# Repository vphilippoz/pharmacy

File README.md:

# Pharmacy Cross Display
<p align="left">
    
</p>

A miniature pharmacy cross display made of LED matrices.

This is a fun project to build and decorate you home, or bring at a rave party! The software runs on a ESP32 and controls 5 square LED matrices.

# Features

In its current version, the project has:

- 8 animations
- Button to switch between animations
- Potentiometer to tune brightness and animation speed
- Python script to easily create animation bitmap from a .gif file
- Excel file to easily create animation bitmap from a drawing (in excel file)

Available animations are:

1. Always ON
1. Blink
1. Random (White noise)
1. Cross shrinking
1. Girl dance
1. Fortnite dance
1. Spinning fish
1. Spiral

# Usage

Plug the power connector. The device starts automatically. A short press on the button changes the animation. Turning the knob allows to tune the animation speed. One cycle is between 80 BPM and 250 BPM. When holding the button, the knob controlls the display brightness.

# BOM

This list is not intended to be a shopping list. It enumerates everything needed to make the Pharmacy Cross Display, but use what you have and adapt the design as needed.

## Electronics

- 5V power supply
- Custom-made PCBs (one of each)
- ESP32-C6-DevKit
- 3 HT16K33 modules (Adafruit 1427)
- 5 green LED matrices (Adafruit 1623)
- 1 10kOhm rotary potentiometer
- 1 THT 10kOhm resistor
- 1 push button
- 1 barrel power connector
- Cables
- Headers for ESP32, HT16k33 and peripherals

## Casing

- 4-parts 3D printed custom casing. I printed mine in black PETG.
- 2 M2.5x4 socket head cap screws
- 10 M2.5x8 socket head cap screws
- Optional: 6 M2.5 washers

## Tools

- 3D printer
- 2mm allen key
- Soldering iron
- Solder
- Set of pliers

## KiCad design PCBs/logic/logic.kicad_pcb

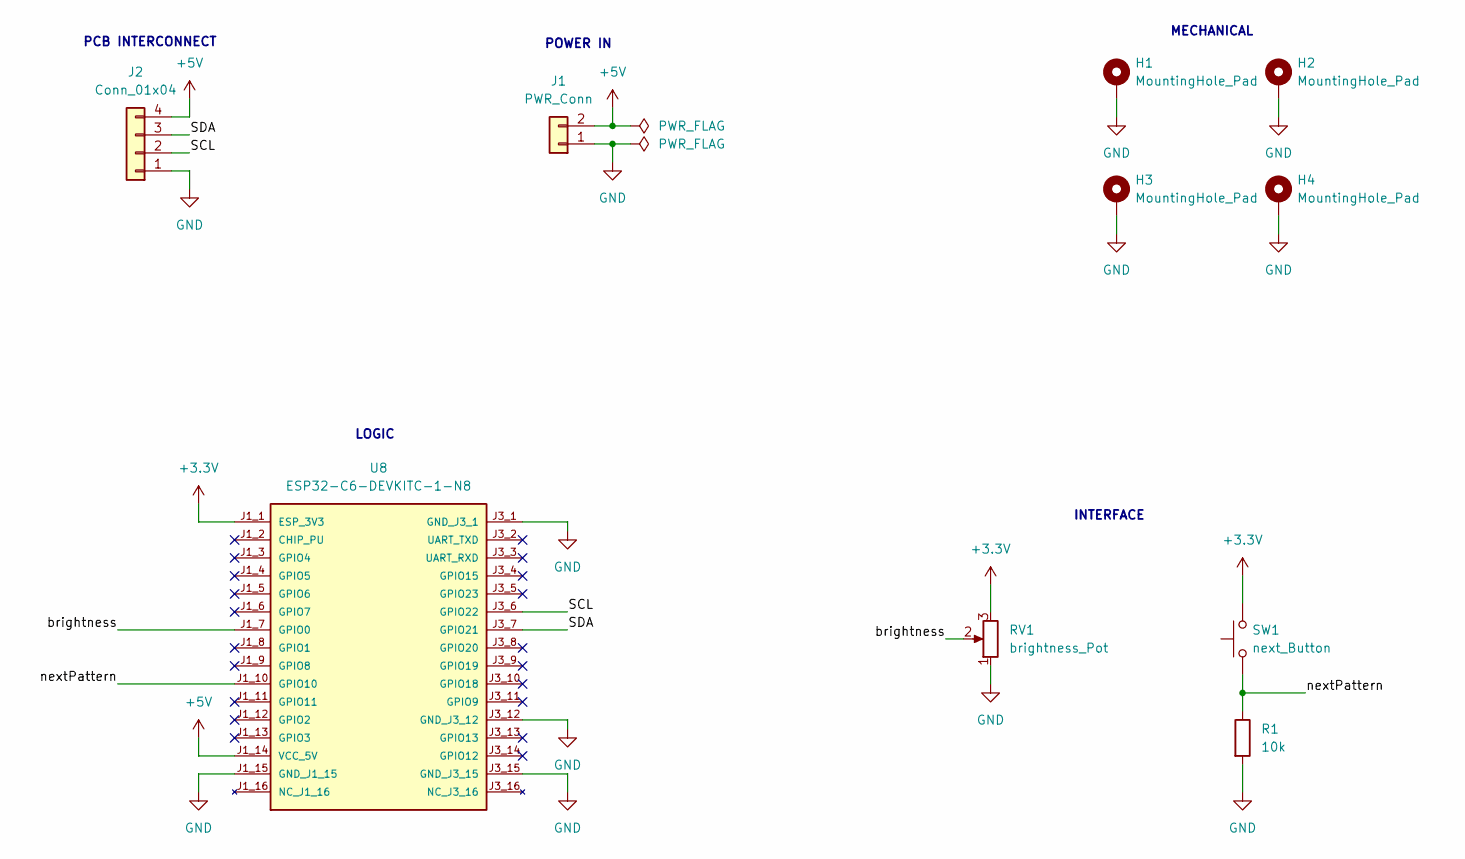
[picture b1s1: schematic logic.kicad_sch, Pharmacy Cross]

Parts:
H1, H2, H3, H4: MountingHole_Pad; MountingHole_2.7mm_M2.5_ISO7380_Pad
J1: PWR_Conn; BarrelJack_Horizontal
J2: Conn_01x04; PinHeader_1x04_P2.54mm_Vertical
R1: 10k; R_Axial_DIN0207_L6.3mm_D2.5mm_P10.16mm_Horizontal
RV1: brightness_Pot; PinHeader_1x03_P2.54mm_Vertical
SW1: next_Button; PinHeader_1x02_P2.54mm_Vertical
U8: ESP32-C6-DEVKITC-1-N8; MODULE_ESP32-C6-DEVKITC-1-N8; PARTREV 1.3

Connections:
+3.3V: RV1.3, SW1.2, U8.J1_1 (ESP_3V3)
+5V: J1.2, J2.4, U8.J1_14 (VCC_5V)
/SCL: J2.2, U8.J3_6 (GPIO22)
/SDA: J2.3, U8.J3_7 (GPIO21)
/brightness: RV1.2, U8.J1_7 (GPIO0)
/nextPattern: R1.1, SW1.1, U8.J1_10 (GPIO10)
GND: H1.1, H2.1, H3.1, H4.1, J1.1, J2.1, R1.2, RV1.1, U8.J1_15 (GND_J1_15), U8.J3_1 (GND_J3_1), U8.J3_12 (GND_J3_12), U8.J3_15 (GND_J3_15)

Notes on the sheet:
LOGIC
PCB INTERCONNECT
POWER IN
INTERFACE
MECHANICAL

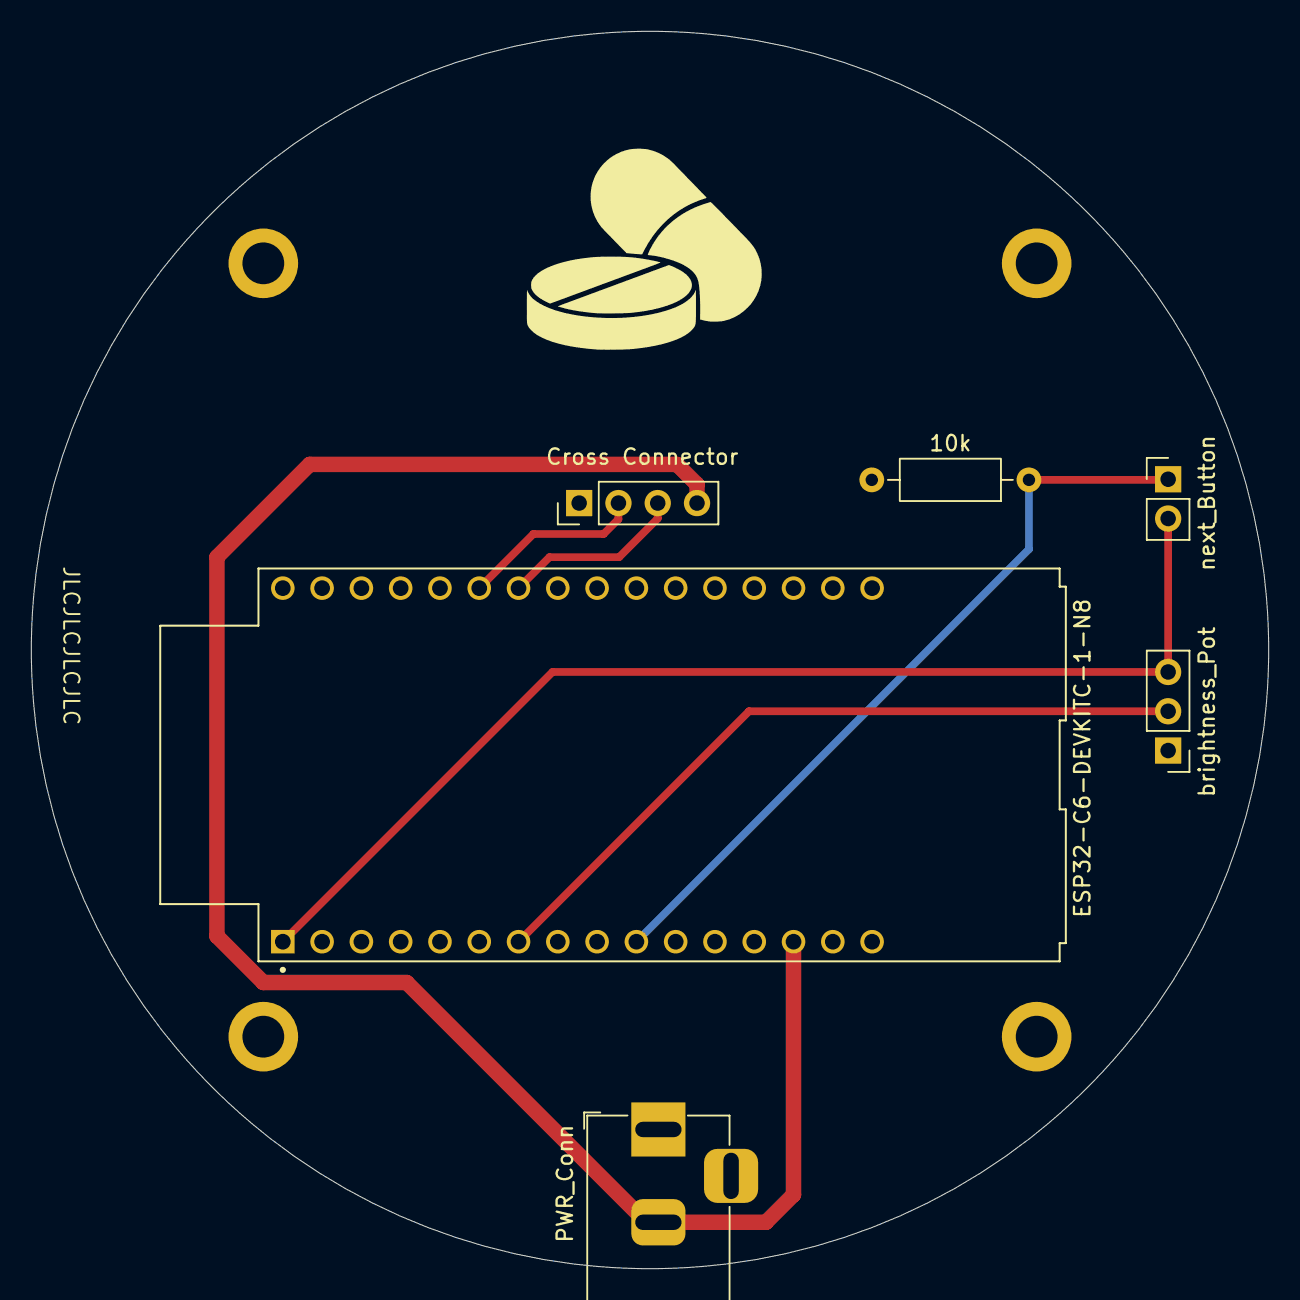
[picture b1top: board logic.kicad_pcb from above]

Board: 2 copper layers, 80.0 x 80.0 mm, 10 parts (0 on the bottom side), 7 nets.

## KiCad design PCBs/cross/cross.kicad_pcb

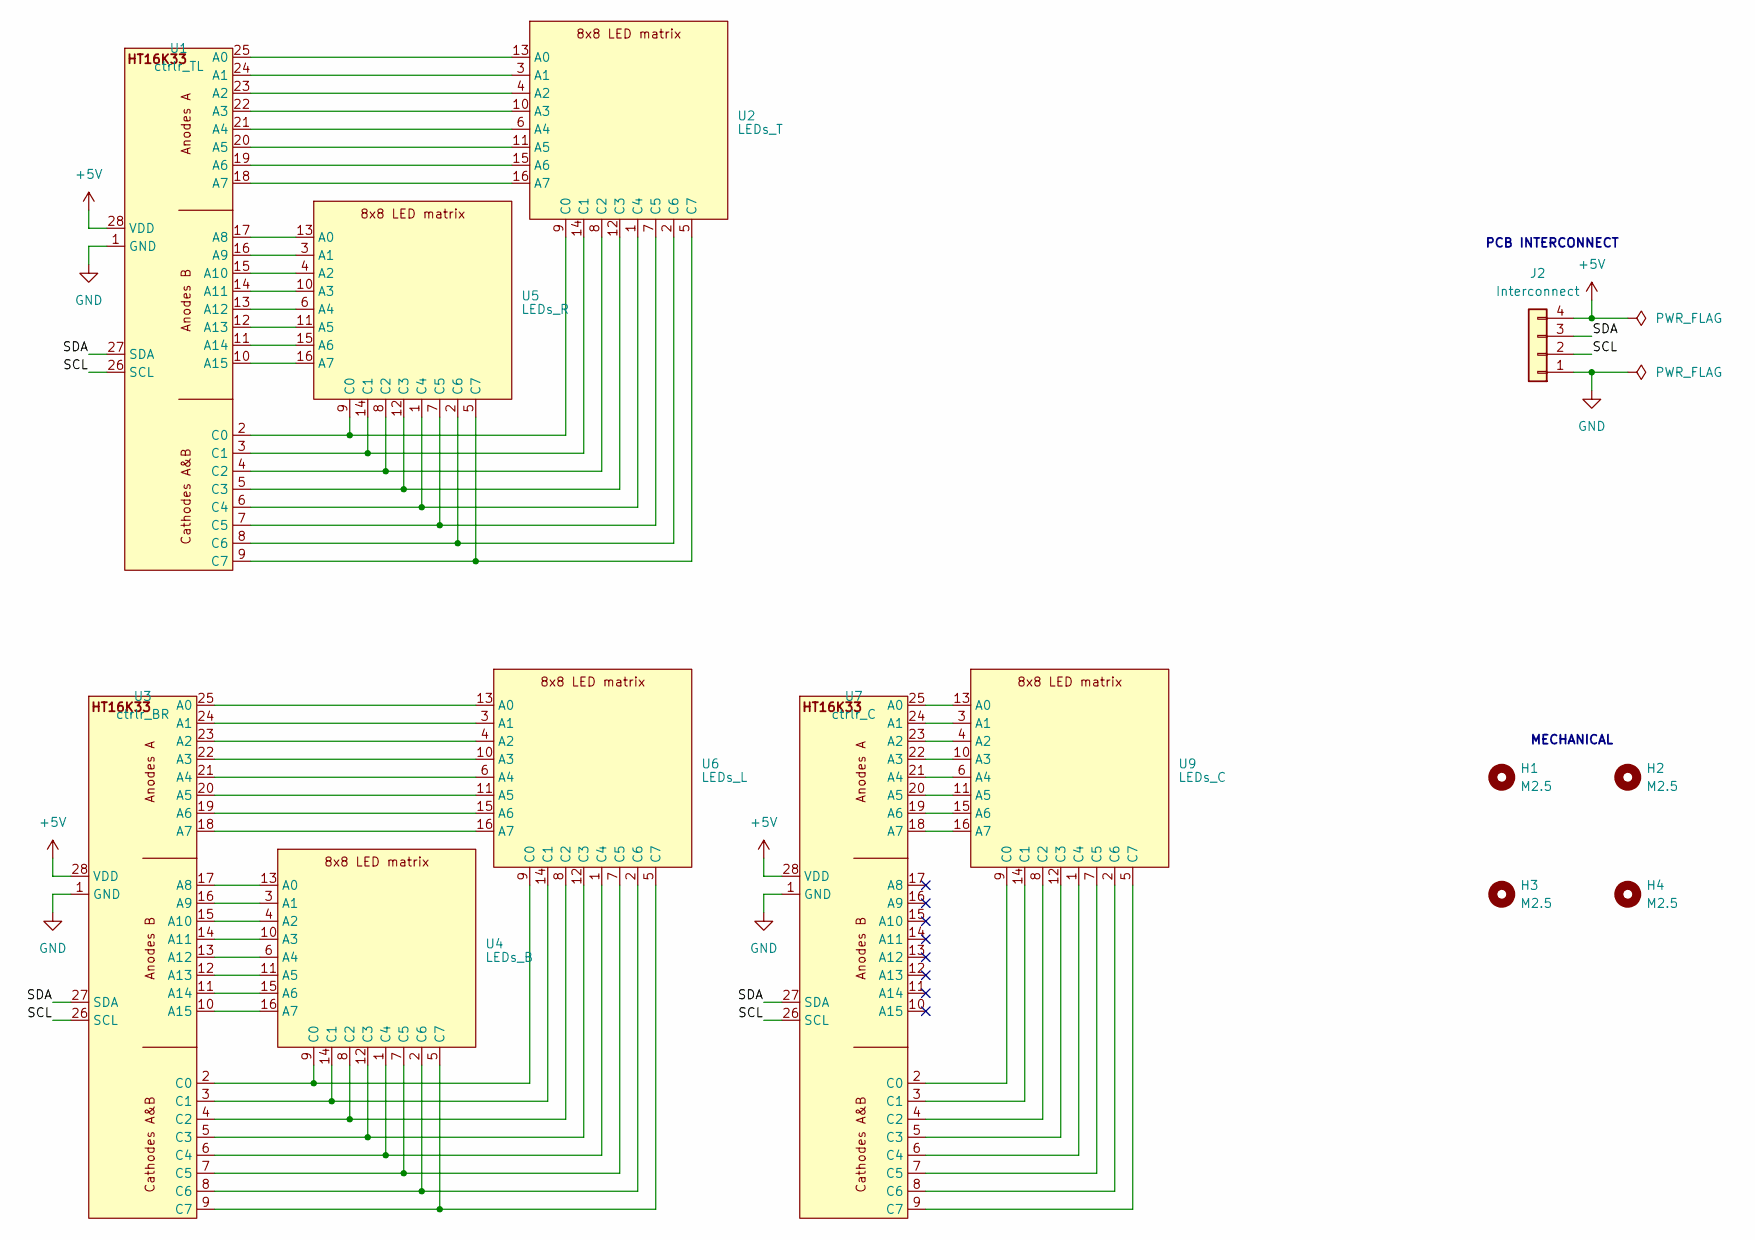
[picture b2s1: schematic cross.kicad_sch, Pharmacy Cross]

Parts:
H1, H2, H3, H4: M2.5; MountingHole_2.7mm_M2.5
J2: Interconnect; PinHeader_1x04_P2.54mm_Vertical
U1: ctrlr_TL; HT16K33
U2: LEDs_T; KWM-30881
U3: ctrlr_BR; HT16K33
U4: LEDs_B; KWM-30881
U5: LEDs_R; KWM-30881
U6: LEDs_L; KWM-30881
U7: ctrlr_C; HT16K33
U9: LEDs_C; KWM-30881

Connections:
+5V: J2.4, U1.28 (VDD), U3.28 (VDD), U7.28 (VDD)
/SCL: J2.2, U1.26 (SCL), U3.26 (SCL), U7.26 (SCL)
/SDA: J2.3, U1.27 (SDA), U3.27 (SDA), U7.27 (SDA)
GND: J2.1, U1.1 (GND), U3.1 (GND), U7.1 (GND)
unnamed: U1.25 (A0), U2.13 (A0)
unnamed: U1.24 (A1), U2.3 (A1)
unnamed: U1.23 (A2), U2.4 (A2)
unnamed: U1.22 (A3), U2.10 (A3)
unnamed: U1.21 (A4), U2.6 (A4)
unnamed: U1.20 (A5), U2.11 (A5)
unnamed: U1.19 (A6), U2.15 (A6)
unnamed: U1.18 (A7), U2.16 (A7)
unnamed: U1.17 (A8), U5.13 (A0)
unnamed: U1.16 (A9), U5.3 (A1)
unnamed: U1.15 (A10), U5.4 (A2)
unnamed: U1.14 (A11), U5.10 (A3)
unnamed: U1.13 (A12), U5.6 (A4)
unnamed: U1.12 (A13), U5.11 (A5)
unnamed: U1.11 (A14), U5.15 (A6)
unnamed: U1.10 (A15), U5.16 (A7)
unnamed: U1.2 (C0), U2.9 (C0), U5.9 (C0)
unnamed: U1.3 (C1), U2.14 (C1), U5.14 (C1)
unnamed: U1.4 (C2), U2.8 (C2), U5.8 (C2)
unnamed: U1.5 (C3), U2.12 (C3), U5.12 (C3)
unnamed: U1.6 (C4), U2.1 (C4), U5.1 (C4)
unnamed: U1.7 (C5), U2.7 (C5), U5.7 (C5)
unnamed: U1.8 (C6), U2.2 (C6), U5.2 (C6)
unnamed: U1.9 (C7), U2.5 (C7), U5.5 (C7)
unnamed: U3.25 (A0), U6.13 (A0)
unnamed: U3.24 (A1), U6.3 (A1)
unnamed: U3.23 (A2), U6.4 (A2)
unnamed: U3.22 (A3), U6.10 (A3)
unnamed: U3.21 (A4), U6.6 (A4)
unnamed: U3.20 (A5), U6.11 (A5)
unnamed: U3.19 (A6), U6.15 (A6)
unnamed: U3.18 (A7), U6.16 (A7)
unnamed: U3.17 (A8), U4.13 (A0)
unnamed: U3.16 (A9), U4.3 (A1)
unnamed: U3.15 (A10), U4.4 (A2)
unnamed: U3.14 (A11), U4.10 (A3)
unnamed: U3.13 (A12), U4.6 (A4)
unnamed: U3.12 (A13), U4.11 (A5)
unnamed: U3.11 (A14), U4.15 (A6)
unnamed: U3.10 (A15), U4.16 (A7)
unnamed: U3.2 (C0), U4.9 (C0), U6.9 (C0)
unnamed: U3.3 (C1), U4.14 (C1), U6.14 (C1)
unnamed: U3.4 (C2), U4.8 (C2), U6.8 (C2)
unnamed: U3.5 (C3), U4.12 (C3), U6.12 (C3)
unnamed: U3.6 (C4), U4.1 (C4), U6.1 (C4)
unnamed: U3.7 (C5), U4.7 (C5), U6.7 (C5)
unnamed: U3.8 (C6), U4.2 (C6), U6.2 (C6)
unnamed: U3.9 (C7), U4.5 (C7), U6.5 (C7)
unnamed: U7.25 (A0), U9.13 (A0)
unnamed: U7.24 (A1), U9.3 (A1)
unnamed: U7.23 (A2), U9.4 (A2)
unnamed: U7.22 (A3), U9.10 (A3)
unnamed: U7.21 (A4), U9.6 (A4)
unnamed: U7.20 (A5), U9.11 (A5)
unnamed: U7.19 (A6), U9.15 (A6)
unnamed: U7.18 (A7), U9.16 (A7)
unnamed: U7.2 (C0), U9.9 (C0)
unnamed: U7.3 (C1), U9.14 (C1)
unnamed: U7.4 (C2), U9.8 (C2)
unnamed: U7.5 (C3), U9.12 (C3)
unnamed: U7.6 (C4), U9.1 (C4)
unnamed: U7.7 (C5), U9.7 (C5)
unnamed: U7.8 (C6), U9.2 (C6)
unnamed: U7.9 (C7), U9.5 (C7)

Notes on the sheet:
PCB INTERCONNECT
MECHANICAL

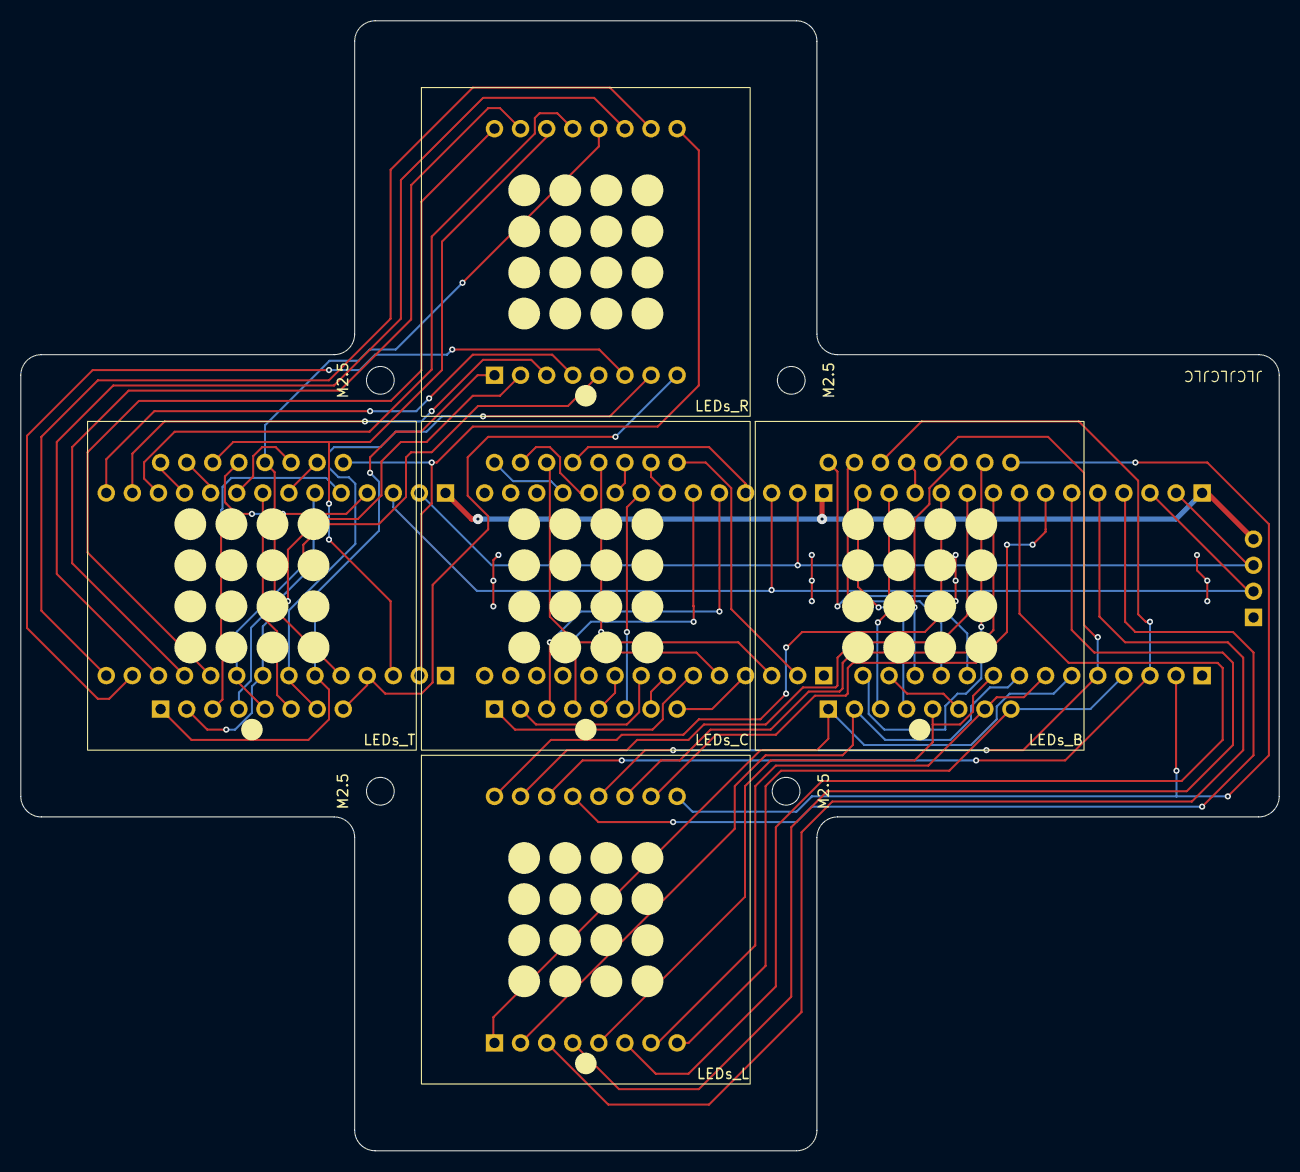
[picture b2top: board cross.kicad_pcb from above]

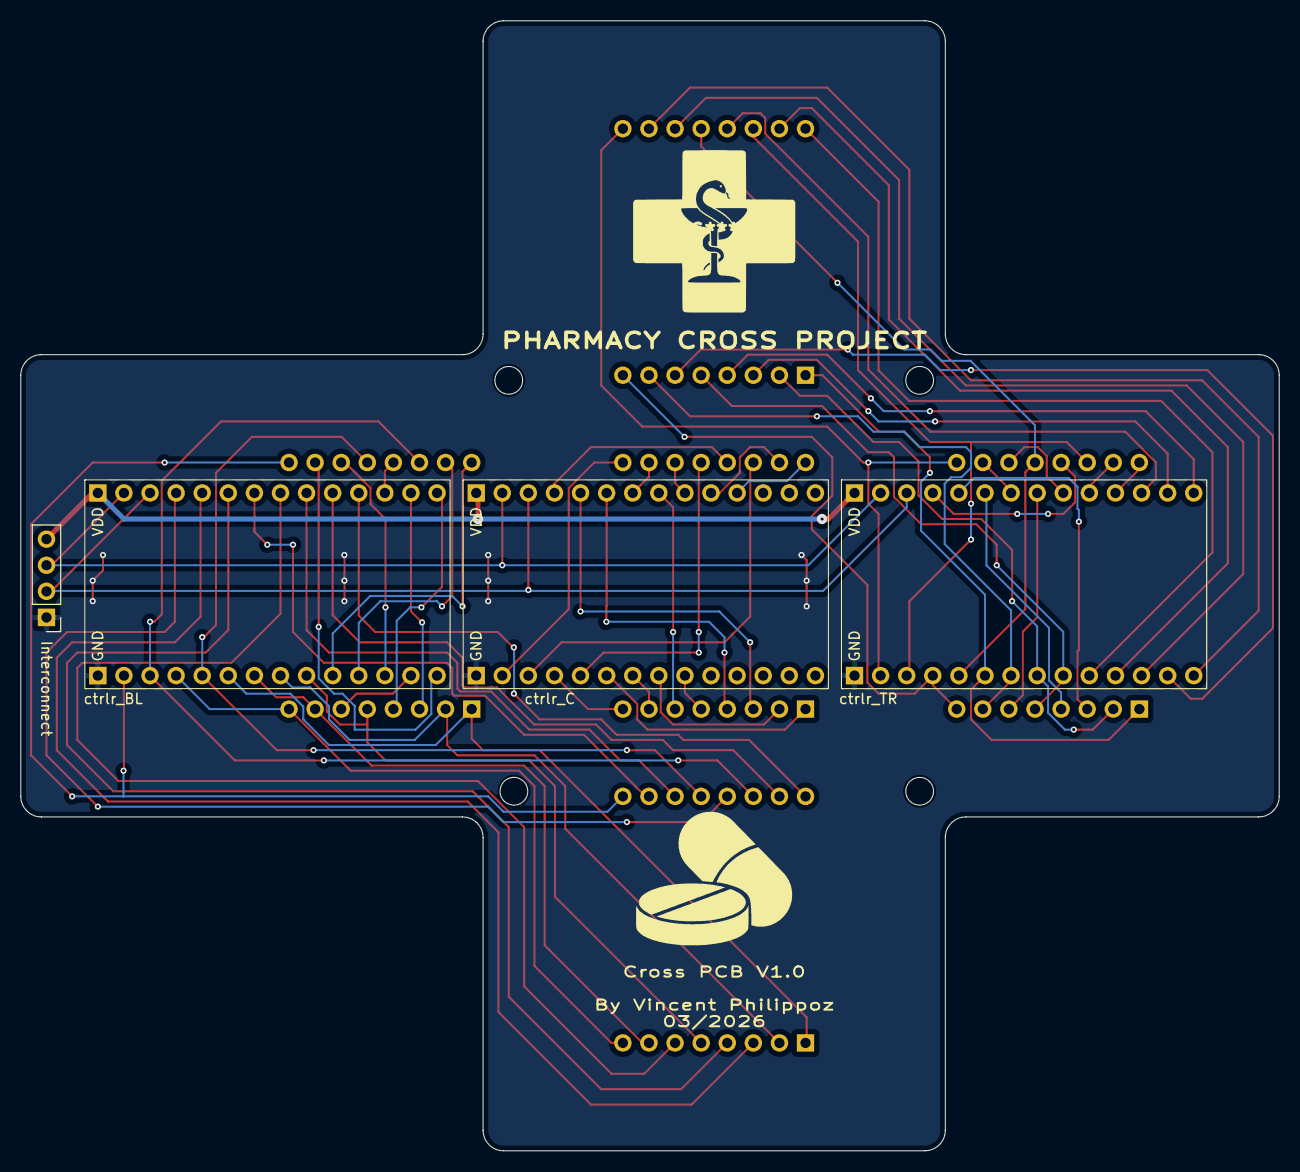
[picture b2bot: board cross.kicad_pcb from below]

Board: 2 copper layers, 122.5 x 110.0 mm, 13 parts (4 on the bottom side), 68 nets.

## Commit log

2026-02-15 Apply KiCad gitignore
2026-02-15 Current state of design
2026-02-15 Added mounting holes to PCB
2026-02-18 Split PCB in two : cross + logic
2026-02-18 Logic PCB finished
2026-02-19 Cross routing 1/3 done
2026-02-21 Cross routing 2/3 done
2026-02-27 Create empty modular structure
2026-02-27 Animation module created, ready to test
2026-02-27 Animation module working on Wokwi
2026-02-27 Started perihperals module
2026-03-02 Peripheral module working on Wokwi
2026-03-02 main.ino done but untested.
2026-03-02 Added Digit display + animation creator
2026-03-02 Add wokwi project zip
2026-03-02 Added shrinking animation
2026-03-02 Improved frame printing in console
2026-03-02 Complete integration works on wokwi
2026-03-02 Fixed pannels rotation to match PCB
2026-03-02 Finished PCBs, ready to order
2026-03-02 Up to date wokwi project
2026-03-10 Works on PCB except animation mapping reversed (MSB->LSB should be LSB->MSB)
2026-03-16 Image creator fixed
2026-03-16 Animations fixed, debouncing btn needed
2026-03-16 minor change
2026-03-16 3D of manufactured PCBs
2026-03-23 Ignore FreeCAD backup files
2026-03-23 Cross case done
2026-03-23 Logic casing without pot&button
2026-03-23 Finished 3D, logic to print
2026-04-01 Logic works
2026-04-04 Added locator to logic top
2026-04-04 STL upload
2026-04-04 Updated doc
2026-04-05 Single knob to control speed and brightness works using button to switch. Now make loop at fixed fast rate and change frame only when necessary.
2026-04-05 Ok-ish, 2 issues: 1) Btn triggers both at press and release. 2) Should add smarter logic to split press and hold
2026-04-06 Hold logic seem ok but btn_state unreliable :(
2026-04-06 Press/hold well separated, everything works!
2026-04-06 Updated readme with new feature
2026-04-06 Added gif to readme
2026-04-07 Update README with version badge smaller image
    Changed the local image reference for the cross animation GIF and added a badge for the latest stable version.
2026-04-10 Added elec diagram to readme
2026-04-12 Created code structure
2026-04-12 open_image works
2026-04-12 image2bitmap works
2026-04-12 bitmap2txt functional
2026-04-12 Minor edit
2026-04-12 bitmap2image working
2026-04-12 GIF 2 ANIM works !! :)
2026-04-12 Added animations and works on hardware
2026-04-12 index mistake in bitmapper
